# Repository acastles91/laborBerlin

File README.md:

Current version of the PCB for the telecine.

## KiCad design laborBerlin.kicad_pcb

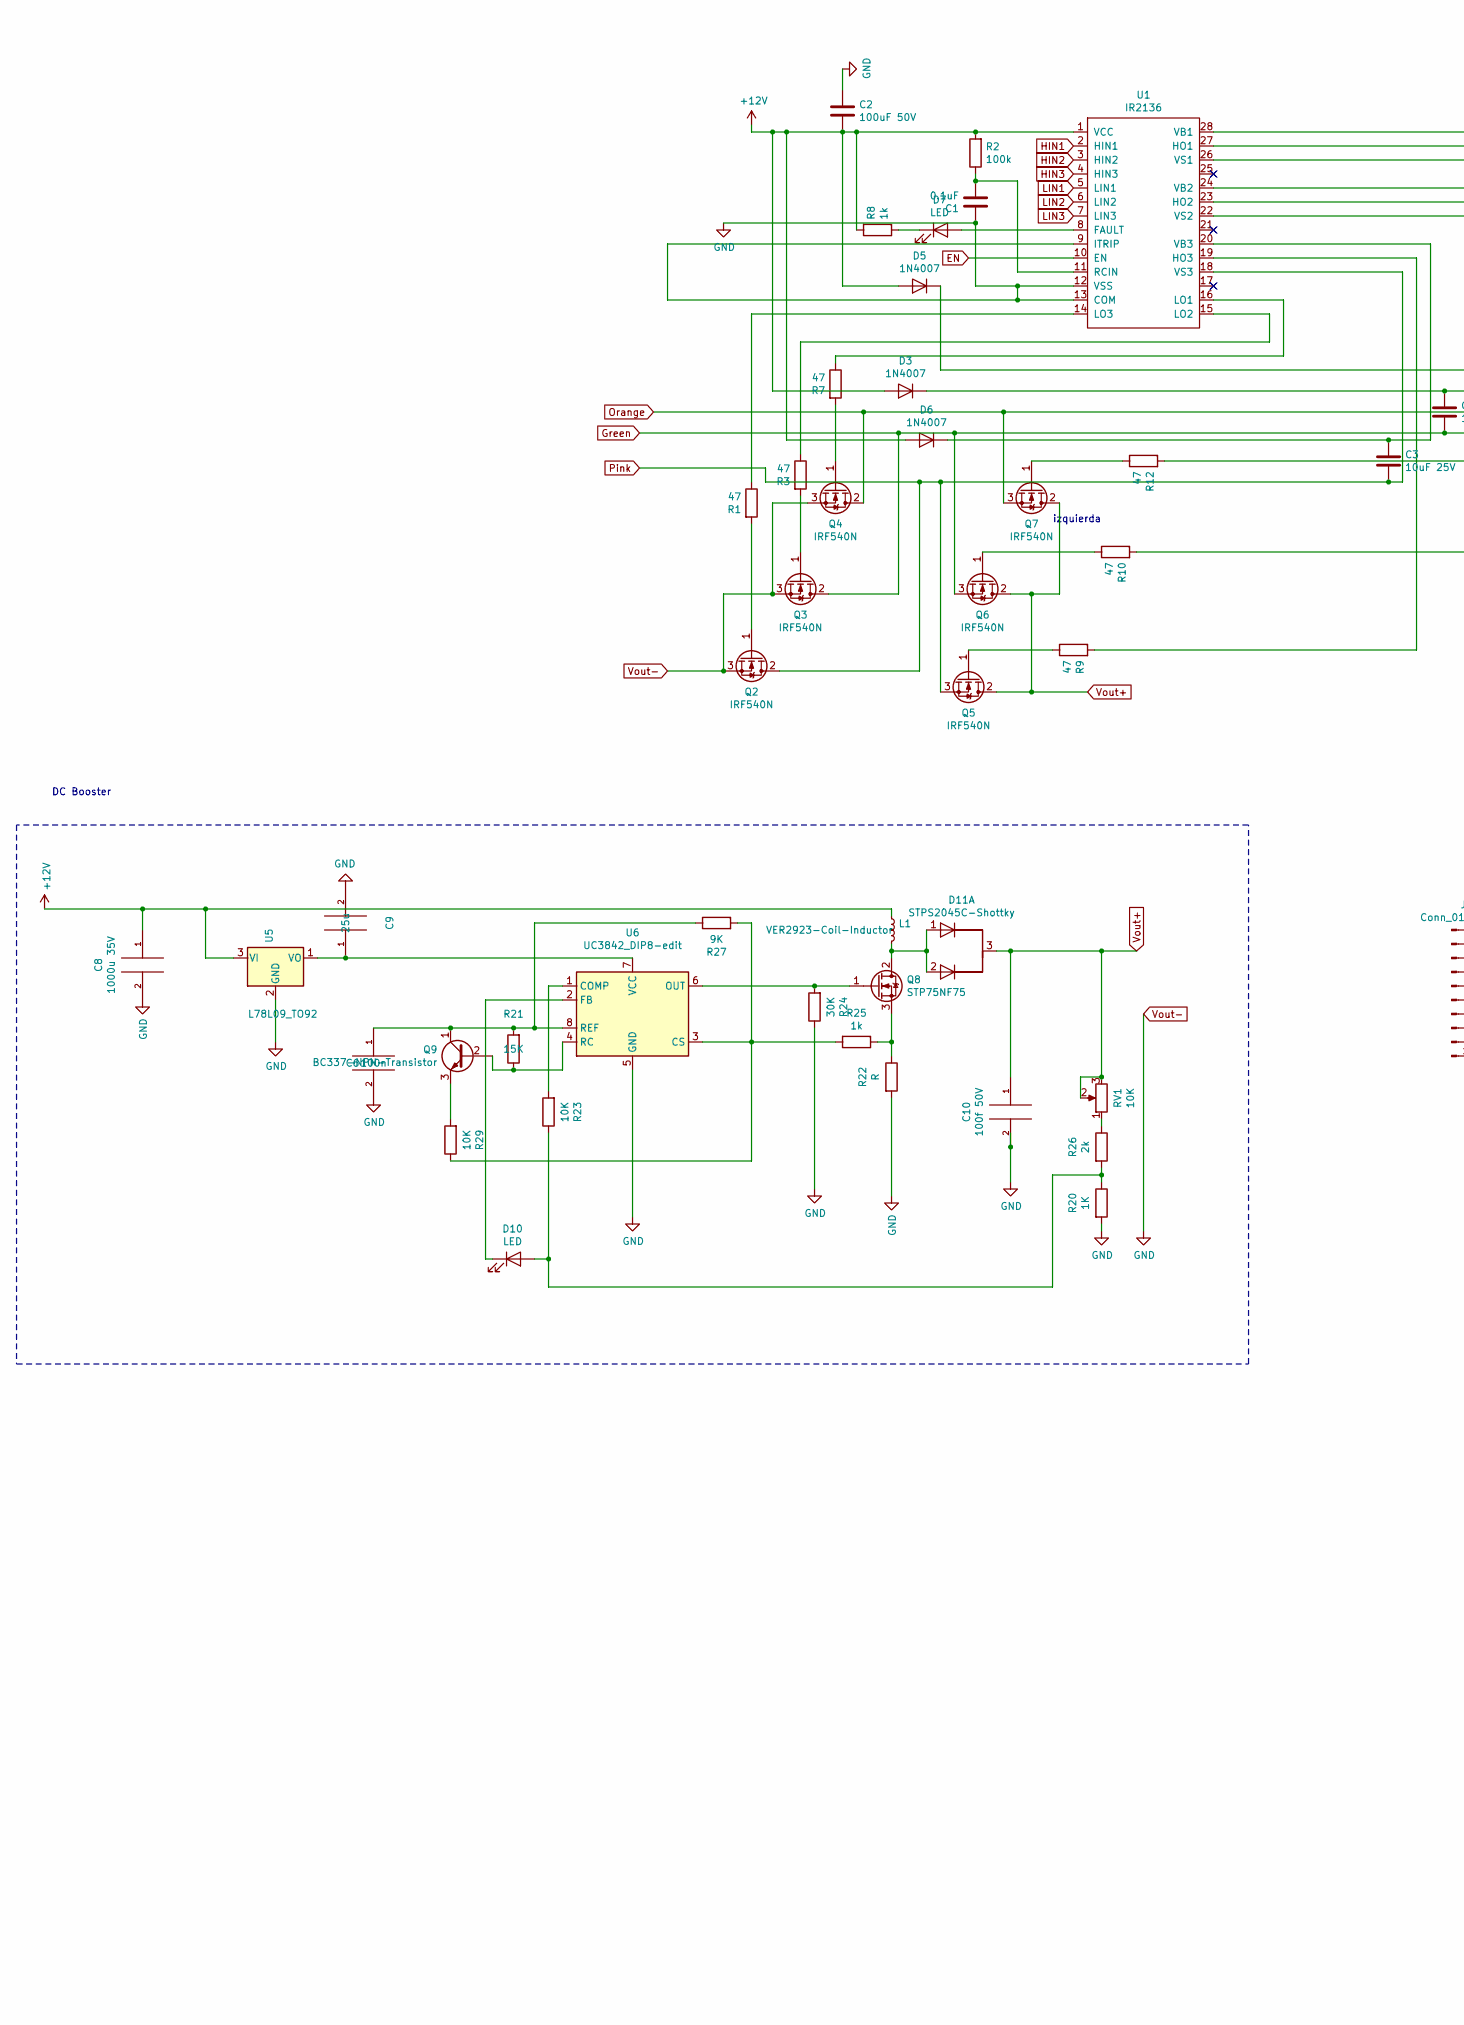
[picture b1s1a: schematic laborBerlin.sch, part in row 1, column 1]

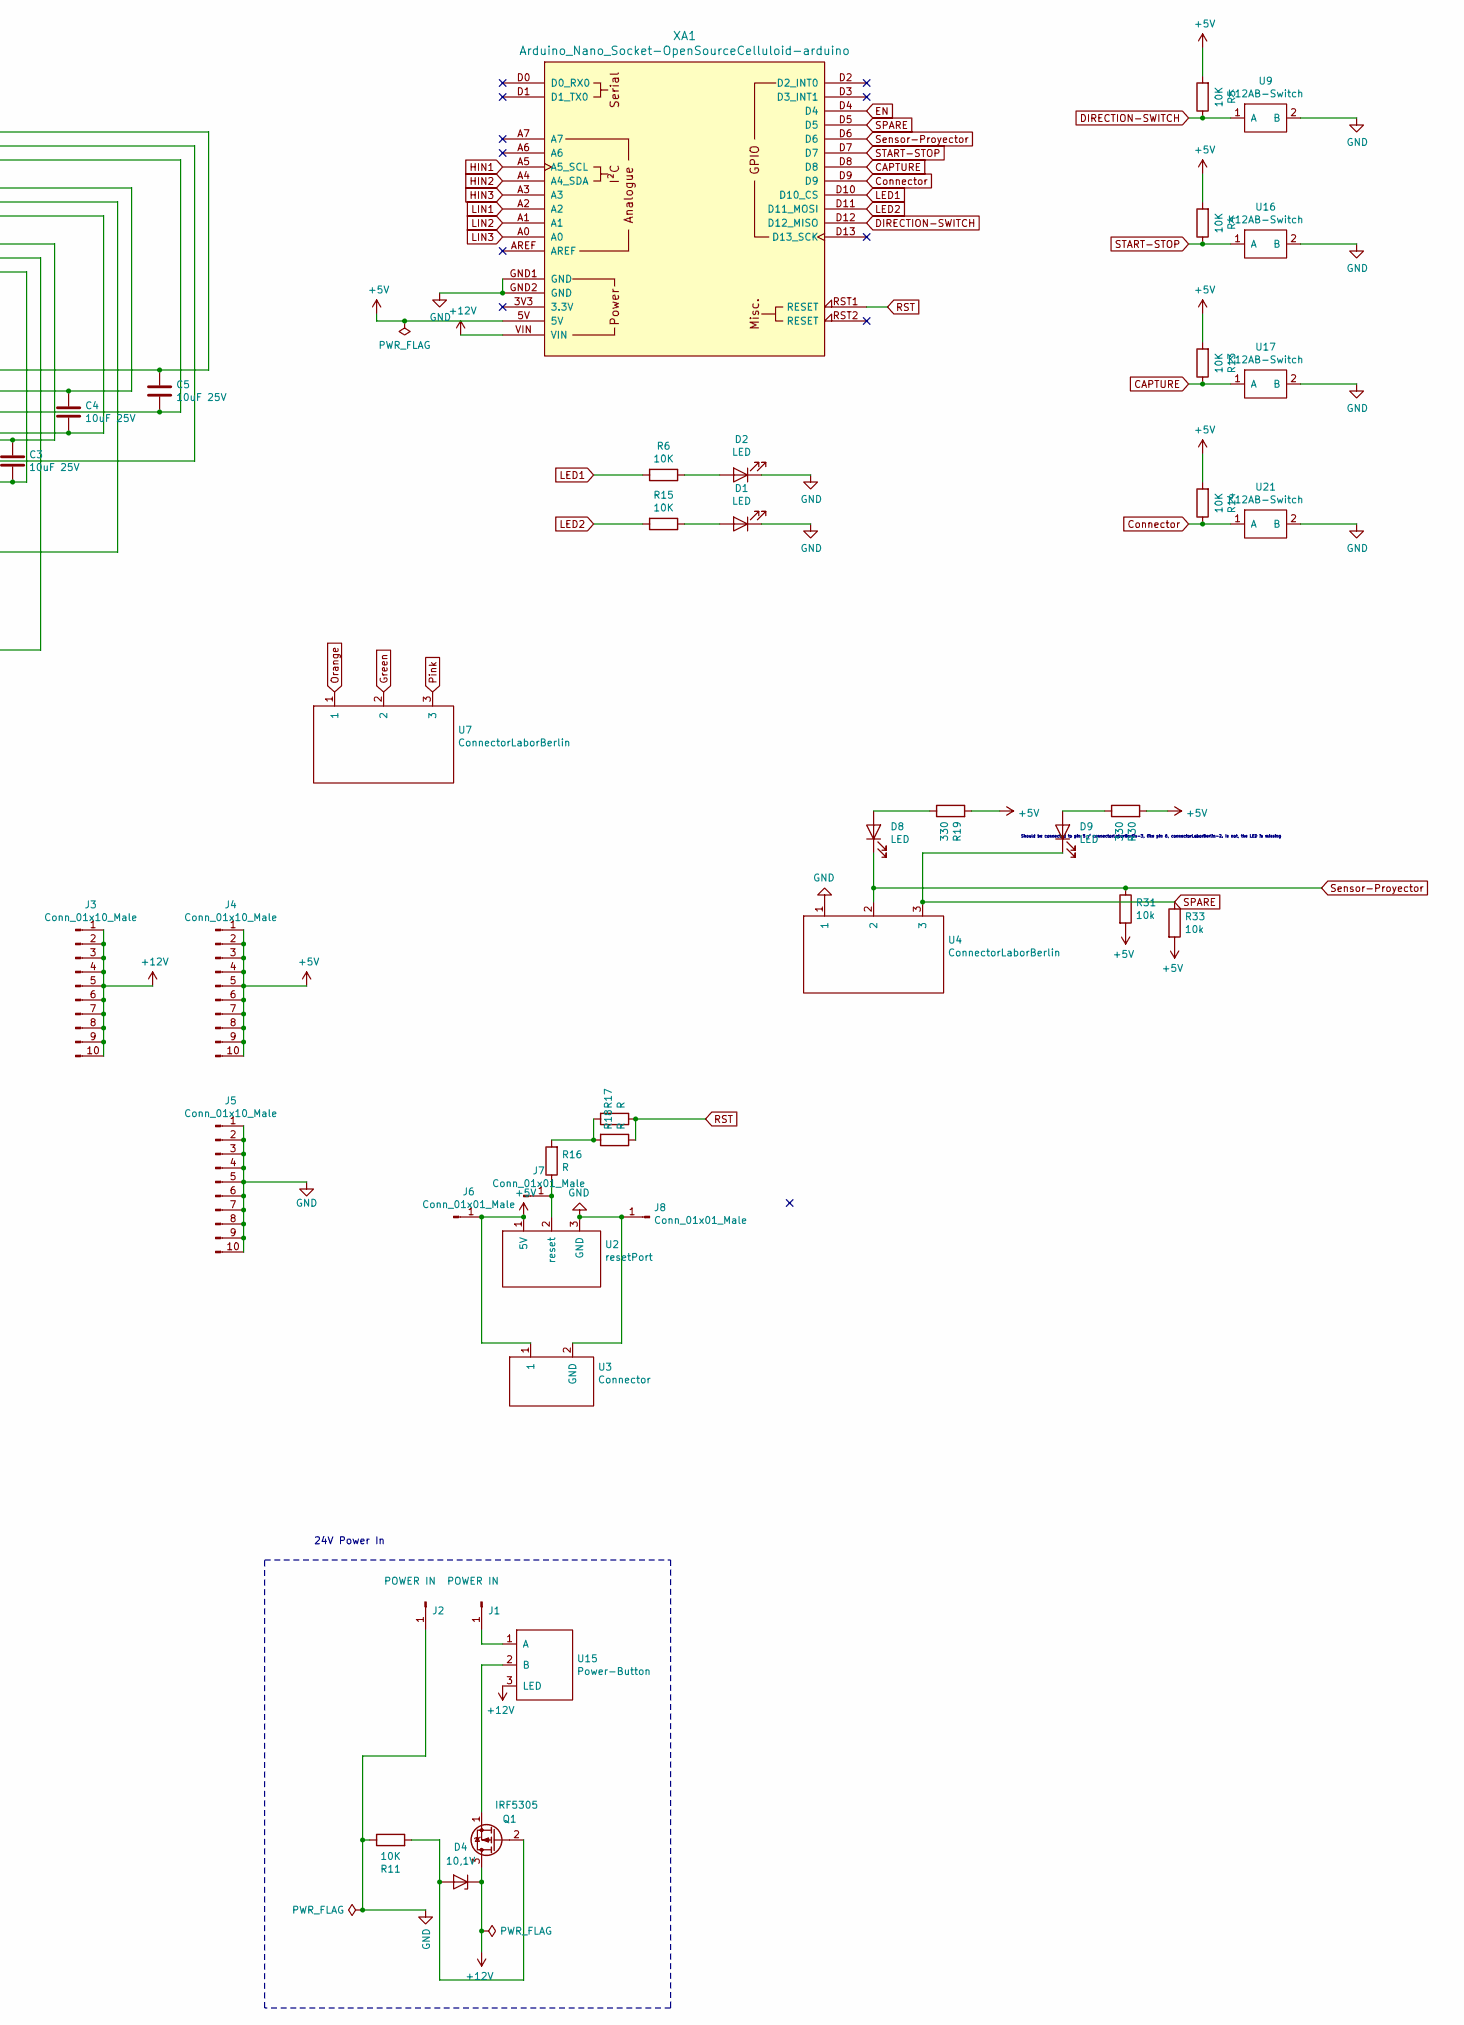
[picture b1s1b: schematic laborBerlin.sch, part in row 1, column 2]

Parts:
C1: 0.1uF; C_Disc_D3.0mm_W1.6mm_P2.50mm
C2: 100uF 50V; CP_Radial_D8.0mm_P2.50mm
C3, C4, C5: 10uF 25V; CP_Radial_D5.0mm_P2.50mm
C6: 100n; C_Disc_D3.0mm_W1.6mm_P2.50mm
C8: 1000u 35V; CP_Radial_D13.0mm_P5.00mm
C9: 25u; C_Disc_D3.0mm_W1.6mm_P2.50mm
C10: 100f 50V; CP_Radial_D13.0mm_P5.00mm
D1, D2: LED; LED_Rectangular_W3.0mm_H2.0mm
D3, D5, D6: 1N4007; D_DO-41_SOD81_P10.16mm_Horizontal
D4: 10,1V; D_T-1_P5.08mm_Horizontal
D7, D8, D9, D10: LED; LED_D3.0mm
D11: STPS2045C-Shottky; STPS2045C
J1, J2: POWER IN; WAGO_PCB_Klemme_1Pol
J3, J4, J5: Conn_01x10_Male; PinHeader_1x10_P2.54mm_Vertical
J6, J7, J8: Conn_01x01_Male; PinHeader_1x01_P2.54mm_Vertical
L1: VER2923-Coil-Inductor
Q1: IRF5305
Q2, Q3, Q4, Q5, Q6, Q7: IRF540N; TO-220-3_Vertical
Q8: STP75NF75; STP75NF75-Mosfet
Q9: BC337-NPN-Transistor
R1, R3, R7, R9, R10, R12: 47; R_Axial_DIN0204_L3.6mm_D1.6mm_P7.62mm_Horizontal
R2: 100k; R_Axial_DIN0204_L3.6mm_D1.6mm_P7.62mm_Horizontal
R4, R5, R6, R11, R13, R14, R15, R23, R29: 10K; R_Axial_DIN0204_L3.6mm_D1.6mm_P7.62mm_Horizontal
R8, R25: 1k; R_Axial_DIN0204_L3.6mm_D1.6mm_P7.62mm_Horizontal
R16, R17, R18, R22: R; R_Axial_DIN0204_L3.6mm_D1.6mm_P7.62mm_Horizontal
R19, R30: 330; R_Axial_DIN0204_L3.6mm_D1.6mm_P7.62mm_Horizontal
R20: 1K; R_Axial_DIN0204_L3.6mm_D1.6mm_P7.62mm_Horizontal
R21: 15K; R_Axial_DIN0204_L3.6mm_D1.6mm_P7.62mm_Horizontal
R24: 30K; R_Axial_DIN0204_L3.6mm_D1.6mm_P7.62mm_Horizontal
R26: 2k; R_Axial_DIN0204_L3.6mm_D1.6mm_P7.62mm_Horizontal
R27: 9K; R_Axial_DIN0204_L3.6mm_D1.6mm_P7.62mm_Horizontal
R31, R33: 10k; R_Axial_DIN0204_L3.6mm_D1.6mm_P7.62mm_Horizontal
RV1: 10K; Potentiometer_Bourns_3299W_Vertical
U1: IR2136; IR2136-Inverter
U2: resetPort; WAGO_PCB_Klemme_3Pol
U3: Connector; WAGO_PCB_Klemme_2Pol
U4, U7: ConnectorLaborBerlin; WAGO_PCB_Klemme_3Pol
U5: L78L09_TO92; TO-92_Inline
U6: UC3842_DIP8-edit; DIP-8_W7.62mm
U9, U16, U17, U21: K12AB-Switch
U15: Power-Button; WAGO_PCB_Klemme_3Pol
XA1: Arduino_Nano_Socket-OpenSourceCelluloid-arduino; Arduino_Nano_Socket

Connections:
+5V: J4.1, J4.2, J4.3, J4.4, J4.5, J4.6, J4.7, J4.8, J4.9, J4.10, J6.1, R4.2, R5.2, R13.2, R14.2, R19.2, R30.2, R31.2, R33.2, U2.1 (5V), U3.1, XA1.5V
+12V: C2.2, C8.1, D3.2 (A), D4.1 (K), D5.2 (A), D6.2 (A), J3.1, J3.2, J3.3, J3.4, J3.5, J3.6, J3.7, J3.8, J3.9, J3.10, L1.1, Q1.3 (D), R2.2, R8.2, U1.1 (VCC), U5.3 (VI), U15.3 (LED), XA1.VIN
CAPTURE: R13.1, U17.1 (A), XA1.D8
Connector: R14.1, U21.1 (A), XA1.D9
DIRECTION-SWITCH: R5.1, U9.1 (A), XA1.D12 (D12_MISO)
EN: U1.10 (EN), XA1.D4
Green: C4.1, Q3.2 (D), Q6.3 (S), U1.22 (VS2), U7.2
HIN1: U1.2 (HIN1), XA1.A5 (A5_SCL)
HIN2: U1.3 (HIN2), XA1.A4 (A4_SDA)
HIN3: U1.4 (HIN3), XA1.A3
LED1: R6.2, XA1.D10 (D10_CS)
LED2: R15.2, XA1.D11 (D11_MOSI)
LIN1: U1.5 (LIN1), XA1.A2
LIN2: U1.6 (LIN2), XA1.A1
LIN3: U1.7 (LIN3), XA1.A0
unnamed: C1.2, R2.1, U1.11 (RCIN)
unnamed: C3.2, D6.1 (K), U1.20 (VB3)
unnamed: C4.2, D3.1 (K), U1.24 (VB2)
unnamed: C5.2, D5.1 (K), U1.28 (VB1)
unnamed: C6.1, Q9.1 (C), R21.2, R27.1, U6.8 (REF)
unnamed: C9.1, U5.1 (VO), U6.7 (VCC)
unnamed: D1.2 (A), R15.1
unnamed: D2.2 (A), R6.1
unnamed: D4.2 (A), Q1.2 (G), R11.2
unnamed: D7.1 (K), R8.1
unnamed: D7.2 (A), U1.8 (FAULT)
unnamed: D8.2 (A), R19.1
unnamed: D9.2 (A), R30.1
unnamed: D10.1 (K), U6.2 (FB)
unnamed: D10.2 (A), R20.1, R23.1, R26.2
unnamed: D11.1 (A), D11.2 (B), L1.2, Q8.2 (D)
unnamed: J1.1, U15.1 (A)
unnamed: J7.1, R16.1, U2.2 (reset)
unnamed: Q1.1 (S), U15.2 (B)
unnamed: Q2.1 (G), R1.2
unnamed: Q3.1 (G), R3.2
unnamed: Q4.1 (G), R7.2
unnamed: Q5.1 (G), R9.1
unnamed: Q6.1 (G), R10.1
unnamed: Q7.1 (G), R12.1
unnamed: Q8.1 (G), R24.2, U6.6 (OUT)
unnamed: Q8.3 (S), R22.1, R25.1
unnamed: Q9.2 (B), R21.1, U6.4 (RC)
unnamed: Q9.3 (E), R29.2
unnamed: R1.1, U1.14 (LO3)
unnamed: R3.1, U1.15 (LO2)
unnamed: R7.1, U1.16 (LO1)
unnamed: R9.2, U1.19 (HO3)
unnamed: R10.2, U1.23 (HO2)
unnamed: R12.2, U1.27 (HO1)
unnamed: R16.2, R17.2, R18.2
unnamed: R23.2, U6.1 (COMP)
unnamed: R25.2, R27.2, R29.1, U6.3 (CS)
unnamed: R26.1, RV1.1
Orange: C5.1, Q4.2 (D), Q7.3 (S), U1.26 (VS1), U7.1
Pink: C3.1, Q2.2 (D), Q5.3 (S), U1.18 (VS3), U7.3
RST: R17.1, R18.1, XA1.RST1 (RESET)
SPARE: D9.1 (K), R33.1, U4.3, XA1.D5
START-STOP: R4.1, U16.1 (A), XA1.D7
Sensor-Proyector: D8.1 (K), R31.1, U4.2, XA1.D6
Vout+: C10.1, D11.3 (B), Q5.2 (D), Q6.2 (D), Q7.2 (D), RV1.2, RV1.3
Vout-: C1.1, C2.1, C6.2, C8.2, C9.2, C10.2, D1.1 (K), D2.1 (K), J2.1, J5.1, J5.2, J5.3, J5.4, J5.5, J5.6, J5.7, J5.8, J5.9, J5.10, J8.1, Q2.3 (S), Q3.3 (S), Q4.3 (S), R11.1, R20.2, R22.2, R24.1, U1.9 (ITRIP), U1.12 (VSS), U1.13 (COM), U2.3 (GND), U3.2 (GND), U4.1, U5.2 (GND), U6.5 (GND), U9.2 (B), U16.2 (B), U17.2 (B), U21.2 (B), XA1.GND1 (GND), XA1.GND2 (GND)

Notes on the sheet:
Should be connected to pin 5 / connectorLaborBerlin-3, like pin 6, connectorLaborBerlin-2. Is not, the LED is missing
izquierda
24V Power In
DC Booster

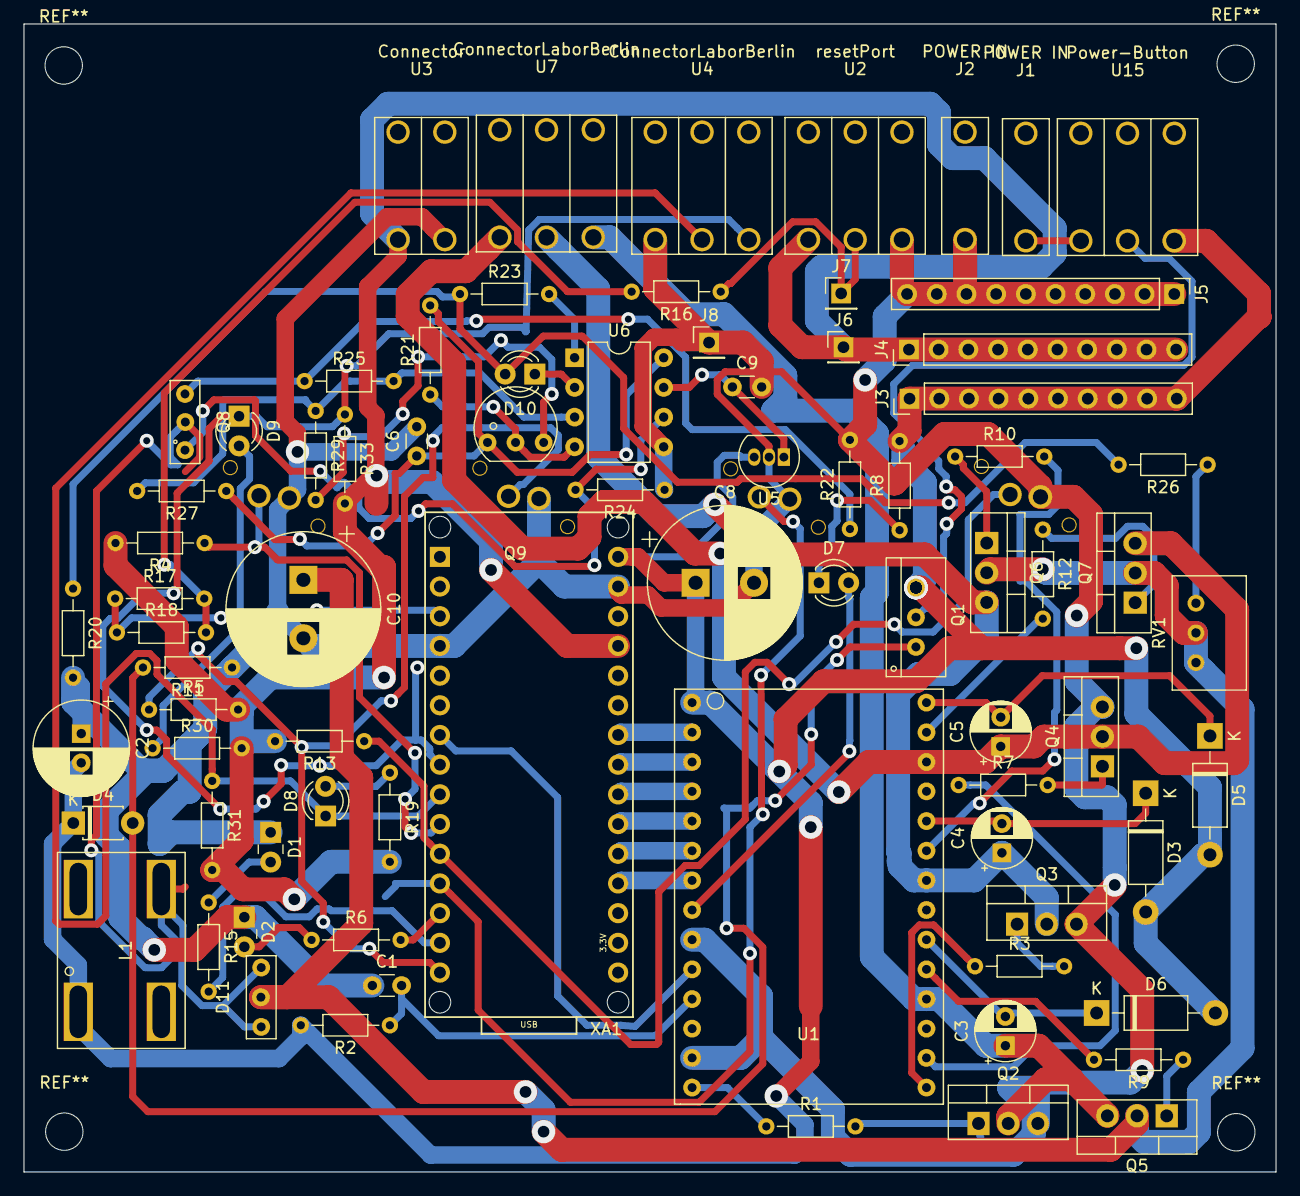
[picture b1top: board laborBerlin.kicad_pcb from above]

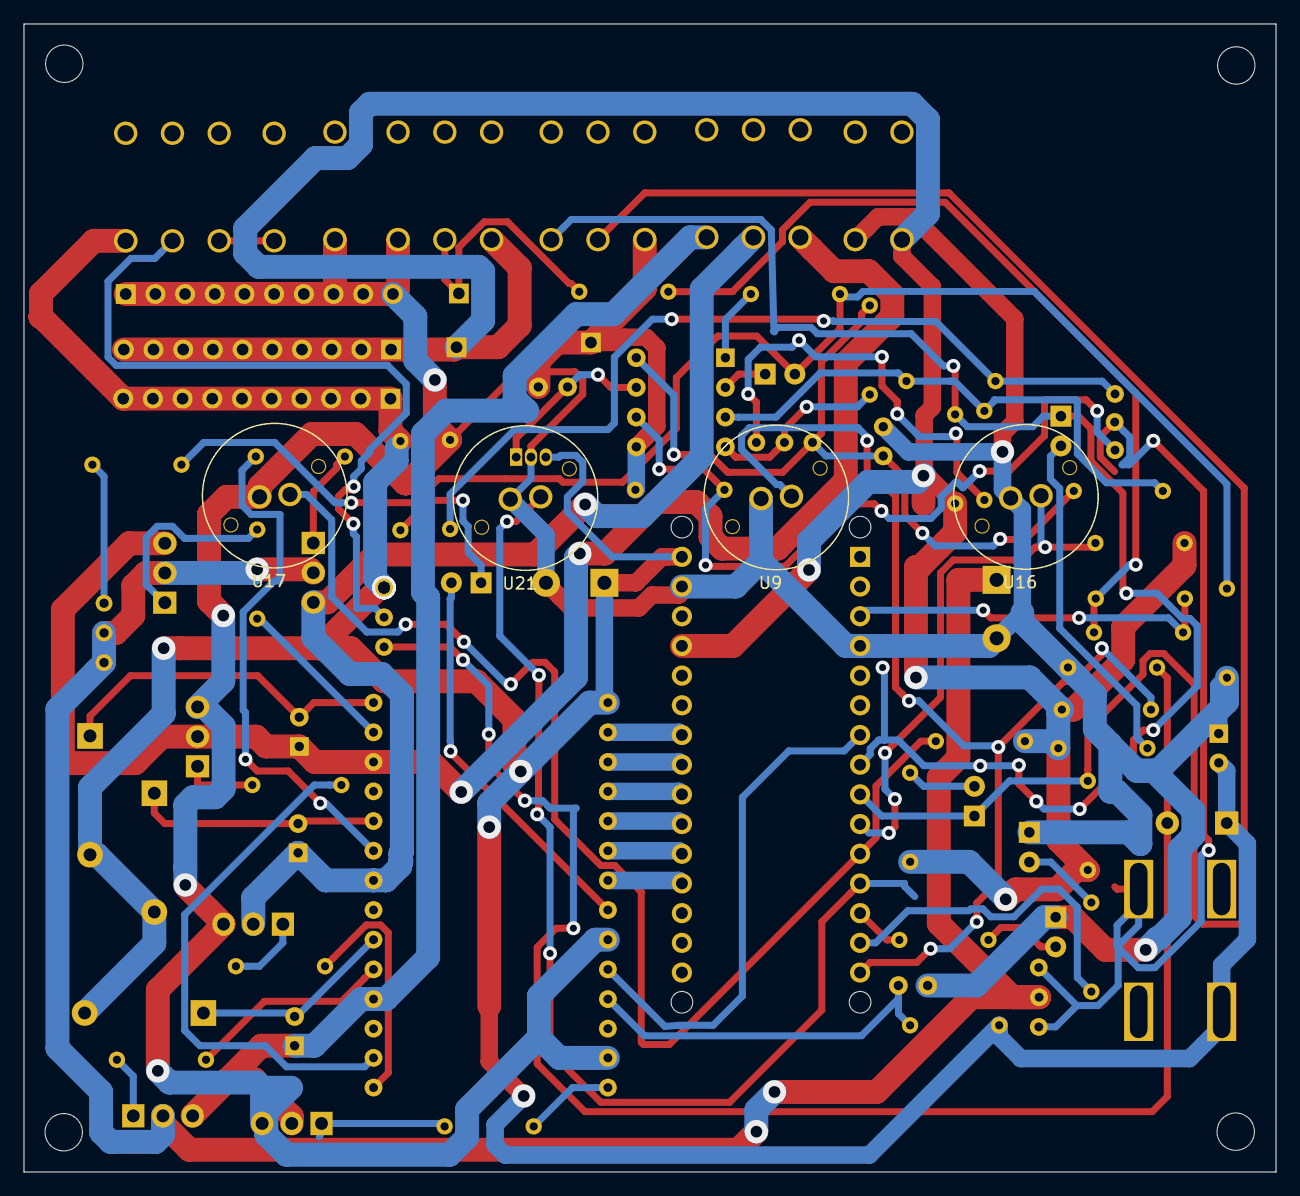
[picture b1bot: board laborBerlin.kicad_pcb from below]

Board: 2 copper layers, 107.1 x 98.2 mm, 82 parts (4 on the bottom side), 62 nets.
